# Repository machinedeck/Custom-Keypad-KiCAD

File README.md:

# Keypad KICAD PCB Design Practice
_Images are not necessarily correct but only detail the current progress of the work._

Steps for PCB design in KiCAD:
- Circuit schematic design **(Schematic Editor)**
  - Add element
  - Define the value (if possible)
  - Define the footprint for later PCB design **(IMPORTANT!)**
- Custom element design **(Symbol Editor)**
  - Define if input, output, etc.
- For custom element, define the footprint **(Footprint Editor)**
  - Specify the size of the pads, etc.
- For the actual PCB design **(PCB Editor)**
  - Define the board, connections, etc.

I used this link to learn about the process: [https://www.youtube.com/watch?v=3FGNw28xBr0](https://www.youtube.com/watch?v=3FGNw28xBr0)

## Things to learn more:
PCB connections

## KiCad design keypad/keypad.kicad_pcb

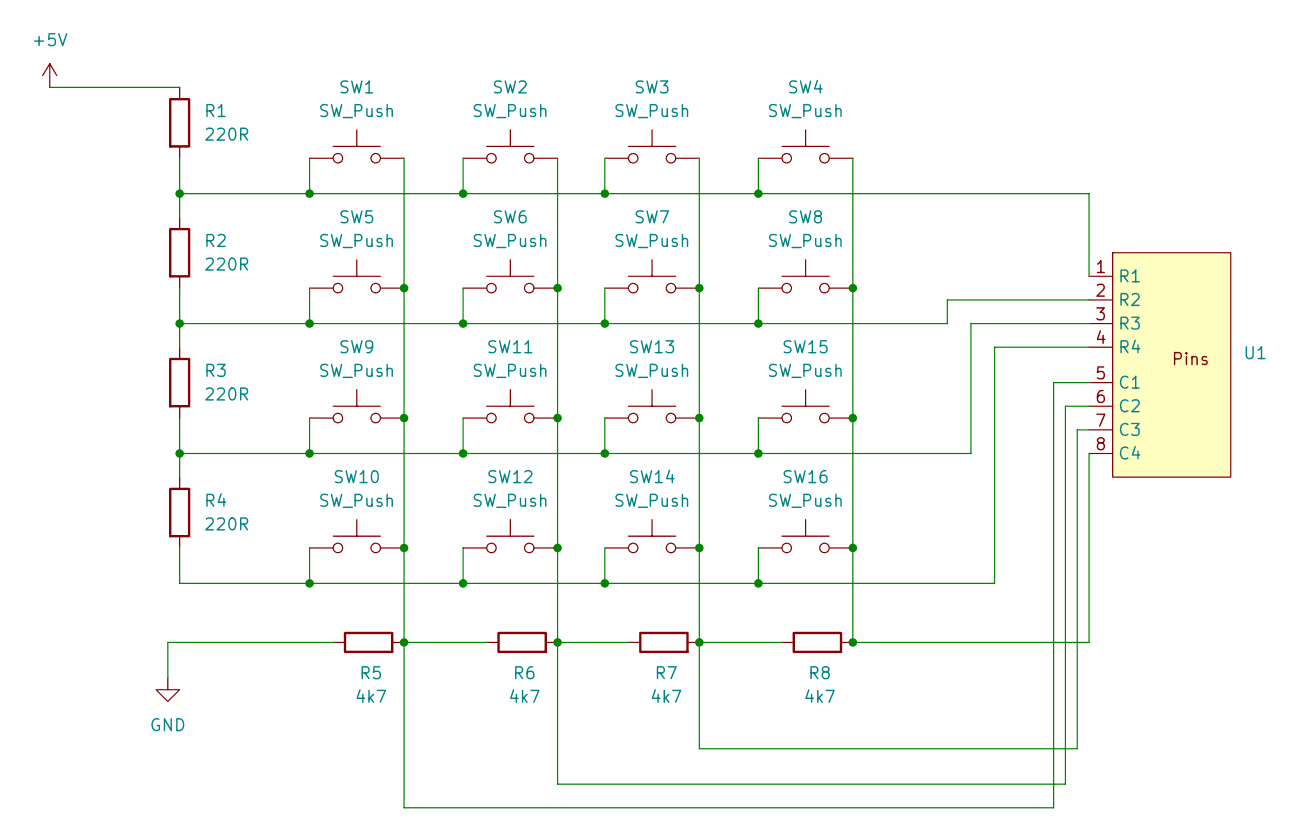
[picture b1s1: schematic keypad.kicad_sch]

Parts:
R1, R2, R3, R4: 220R; C_1206_3216Metric_Pad1.33x1.80mm_HandSolder
R5, R6, R7, R8: 4k7; C_1206_3216Metric_Pad1.33x1.80mm_HandSolder
SW1, SW2, SW3, SW4, SW5, SW6, SW7, SW8, SW9, SW10, SW11, SW12, SW13, SW14, SW15, SW16: SW_Push; SW_Push_1TS009xxxx-xxxx-xxxx_6x6x5mm
U1: eight_pins

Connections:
+5V: R1.1
GND: R5.1
unnamed: R5.2, R6.1, SW1.2, SW5.2, SW9.2, SW10.2, U1.5 (C1)
unnamed: R6.2, R7.1, SW2.2, SW6.2, SW11.2, SW12.2, U1.6 (C2)
unnamed: R7.2, R8.1, SW3.2, SW7.2, SW13.2, SW14.2, U1.7 (C3)
unnamed: R8.2, SW4.2, SW8.2, SW15.2, SW16.2, U1.8 (C4)
unnamed: R1.2, R2.1, SW1.1, SW2.1, SW3.1, SW4.1, U1.1 (R1)
unnamed: R2.2, R3.1, SW5.1, SW6.1, SW7.1, SW8.1, U1.2 (R2)
unnamed: R3.2, R4.1, SW9.1, SW11.1, SW13.1, SW15.1, U1.3 (R3)
unnamed: R4.2, SW10.1, SW12.1, SW14.1, SW16.1, U1.4 (R4)

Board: 2 copper layers, 25 parts (0 on the bottom side), 8 nets, no tracks yet.

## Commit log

2025-11-14 keypad kicad
2025-11-14 images
